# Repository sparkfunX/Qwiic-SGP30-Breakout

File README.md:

Qwiic SGP30 Breakout
===========================================================

[*SparkX SGP30 Breakout (Qwiic) (SPX-14813)*](https://www.sparkfun.com/products/14813)

The SGP30 is an indoor air quality sensor equipped with an I<sup>2</sup>C interface. It outputs equivalent CO<sub>2</sub> in ppm and Total Volatile Organic Compounds (TVOC) in ppb. The sensor also gives access to its raw measurement values of Ethanol and H<sub>2</sub>. 

The SGP30 boasts high stability with low long term drift. With its continuous baseline compensation algorithm, readings stay accurate over time. You can even fine tune your readings by interfacing with an external humidity sensor to add humidity compensation.
While the CCS811 requires a burn-in of 48 hours and a run-in of 20 minutes the SGP30 is ready to go after just 15 seconds.

This board is one of our many [Qwiic](https://www.sparkfun.com/qwiic) compatible boards! Simply plug and go. No soldering, no figuring out which is SDA or SCL, and no voltage regulation or translation required!

SparkFun labored with love to create this. Feel like supporting open source hardware? 
Buy a [board](https://www.sparkfun.com/products/14813) from SparkFun!

Repository Contents
-------------------

* **/Hardware** - Eagle design files (.brd, .sch)

Library
--------------
* **[Arduino Library](https://github.com/sparkfun/SparkFun_SGP30_Library)** - Library for SGP30

License Information
-------------------

This product is _**open source**_! 

If you have any questions or concerns on licensing, please contact techsupport@sparkfun.com.

Please use, reuse, and modify these files as you see fit. Please maintain attribution to SparkFun Electronics and release any derivative under the same license.

Distributed as-is; no warranty is given.

- Your friends at SparkFun.

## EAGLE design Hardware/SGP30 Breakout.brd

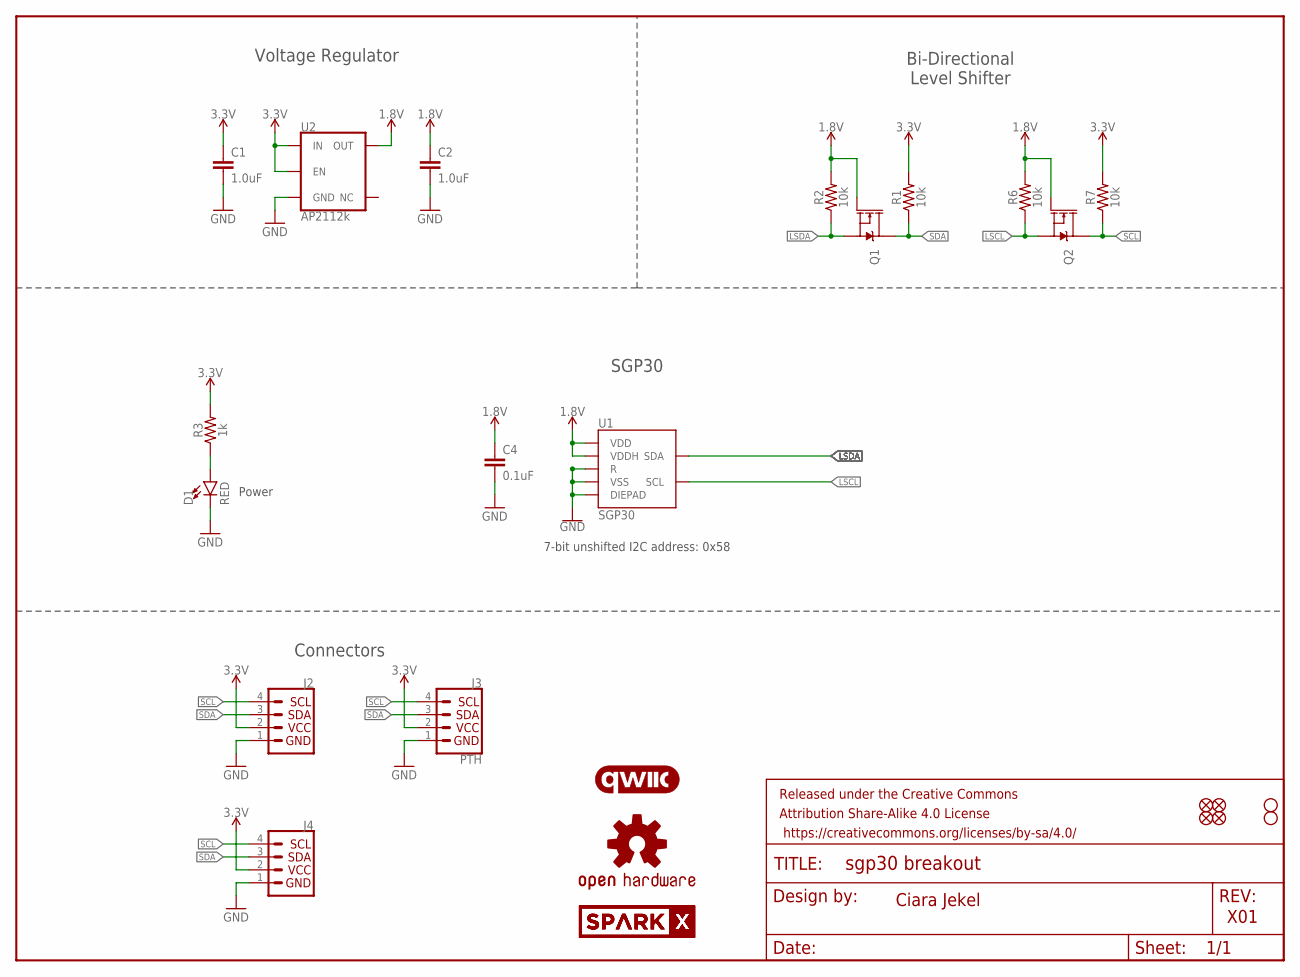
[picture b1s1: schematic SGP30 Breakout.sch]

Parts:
C1, C2: 1.0uF; 0603
C4: 0.1uF; 0603
D1: RED; LED-0603
FRAME1: FRAME-LETTER; CREATIVE_COMMONS
J2, J4: QWIIC_CONNECTORJS-1MM; 1X04_1MM_RA
J3: PTH; 1X04_NO_SILK
JP1, JP2, JP5, JP6: FIDUCIALUFIDUCIAL; MICRO-FIDUCIAL
JP3, JP4: STAND-OFF
LOGO1: OSHW-LOGOMINI; OSHW-LOGO-MINI
Q1, Q2: MOSFET-NCH-BSS138; SOT23-3
R1, R2, R6, R7: 10k; 0603
R3: 1k; 0603
U1: SGP30
U2: AP2112k; SOT23-5
U$1, U$2: SPARKX-LOGO4; SPARKX-MEDIUM
U$9: QWIIC_LOGO_7MM; QWIIC_7MM

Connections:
1.8V: C2.1, C4.1, Q1.1 (G), Q2.1 (G), R2.2, R6.2, U1.1 (VDD), U1.5 (VDDH), U2.5 (OUT)
3.3V: C1.1, J2.2, J3.2 (VCC), J4.2, R1.2, R3.2, R7.2, U2.1 (IN), U2.3 (EN)
GND: C1.2, C2.2, C4.2, D1.C, J2.1, J3.1 (GND), J4.1, U1.2 (VSS), U1.4 (R), U1.DIEPAD, U2.2 (GND)
LSCL: Q2.2 (S), R6.1, U1.6 (SCL)
LSDA: Q1.2 (S), R2.1, U1.3 (SDA)
unnamed: D1.A, R3.1
SCL: J2.4, J3.4 (SCL), J4.4, Q2.3 (D), R7.1
SDA: J2.3, J3.3 (SDA), J4.3, Q1.3 (D), R1.1

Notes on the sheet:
Ciara Jekel
X01
7-bit unshifted I2C address: 0x58
Power
Bi-Directional Level Shifter
Voltage Regulator
SGP30
Connectors

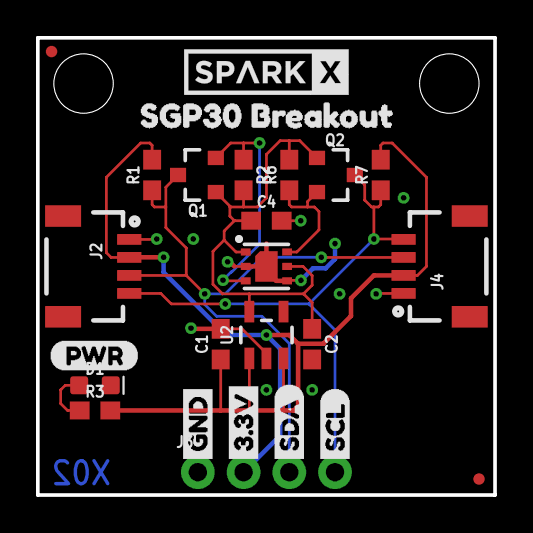
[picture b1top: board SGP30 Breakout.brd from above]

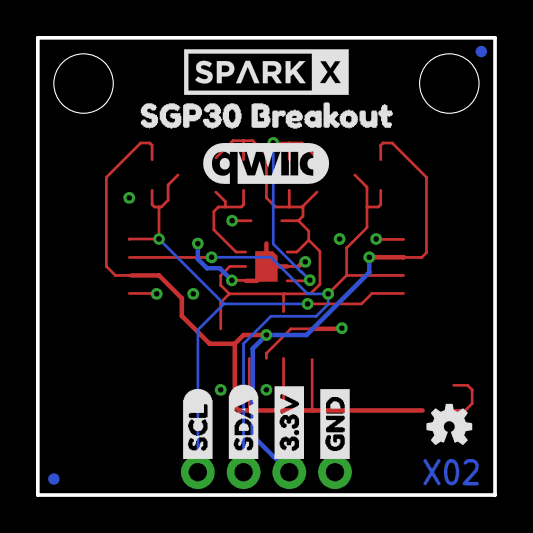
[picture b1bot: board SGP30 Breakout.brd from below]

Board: 2 copper layers, 25.4 x 25.4 mm, 38 parts (10 on the bottom side), 8 nets.

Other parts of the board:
U$3, U$22: GND1
U$4, U$21: 3#3V2
U$5, U$27: SDA8
U$6, U$26: SCL9
U$7, U$8: SGP30_BREAKOUT1
U$10: (PWR)

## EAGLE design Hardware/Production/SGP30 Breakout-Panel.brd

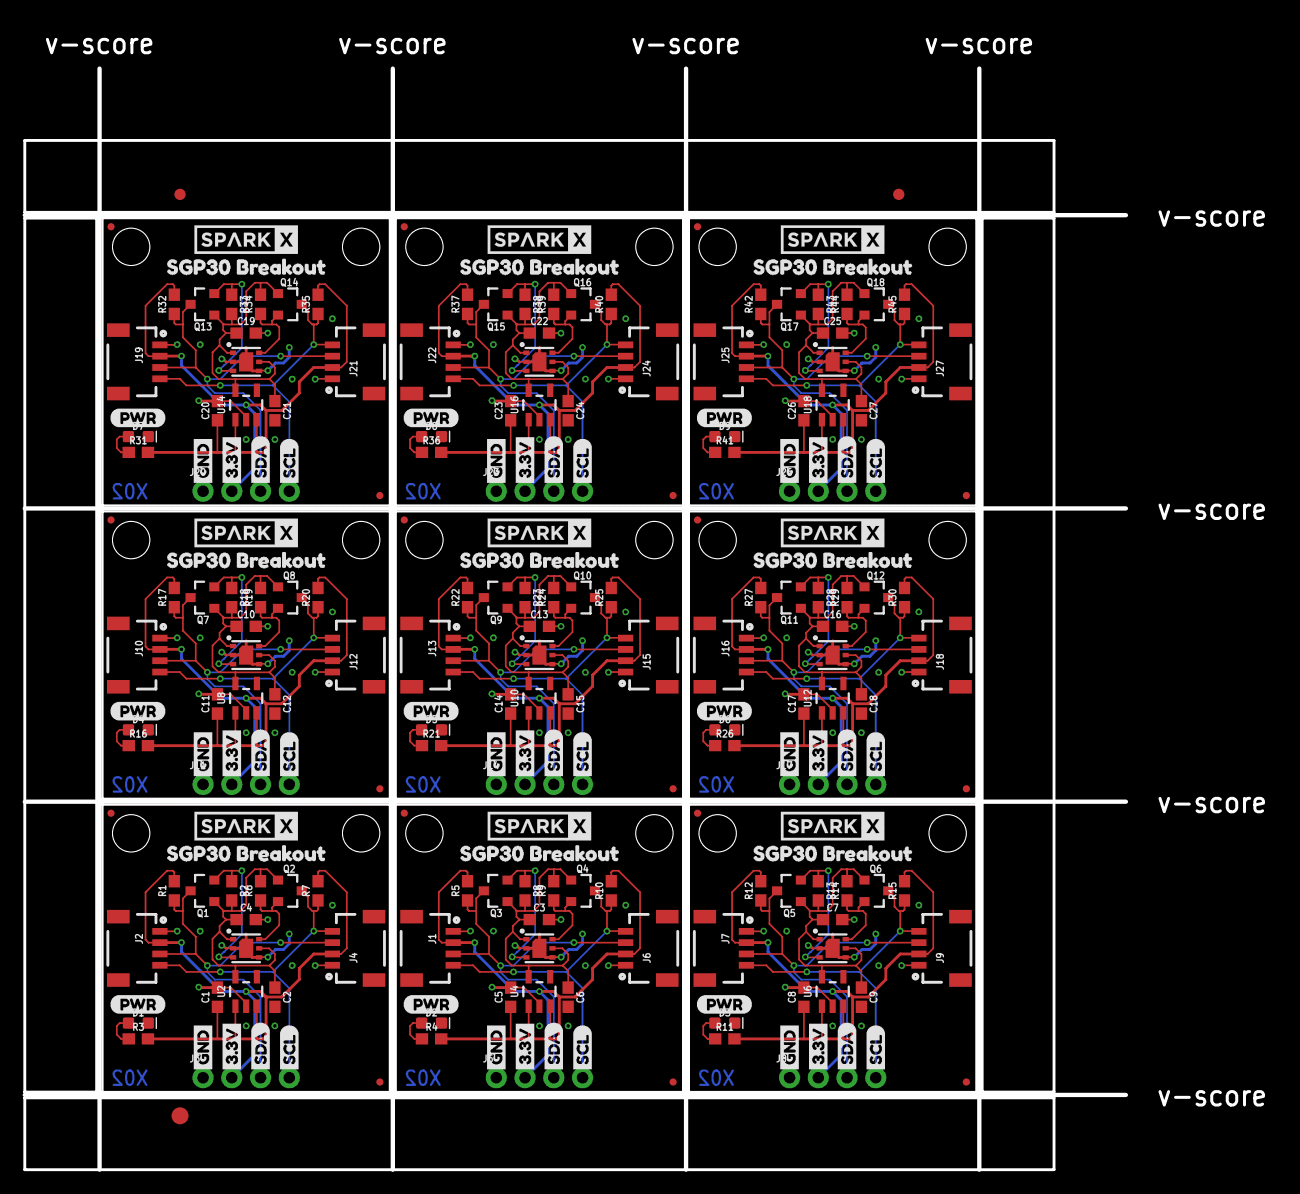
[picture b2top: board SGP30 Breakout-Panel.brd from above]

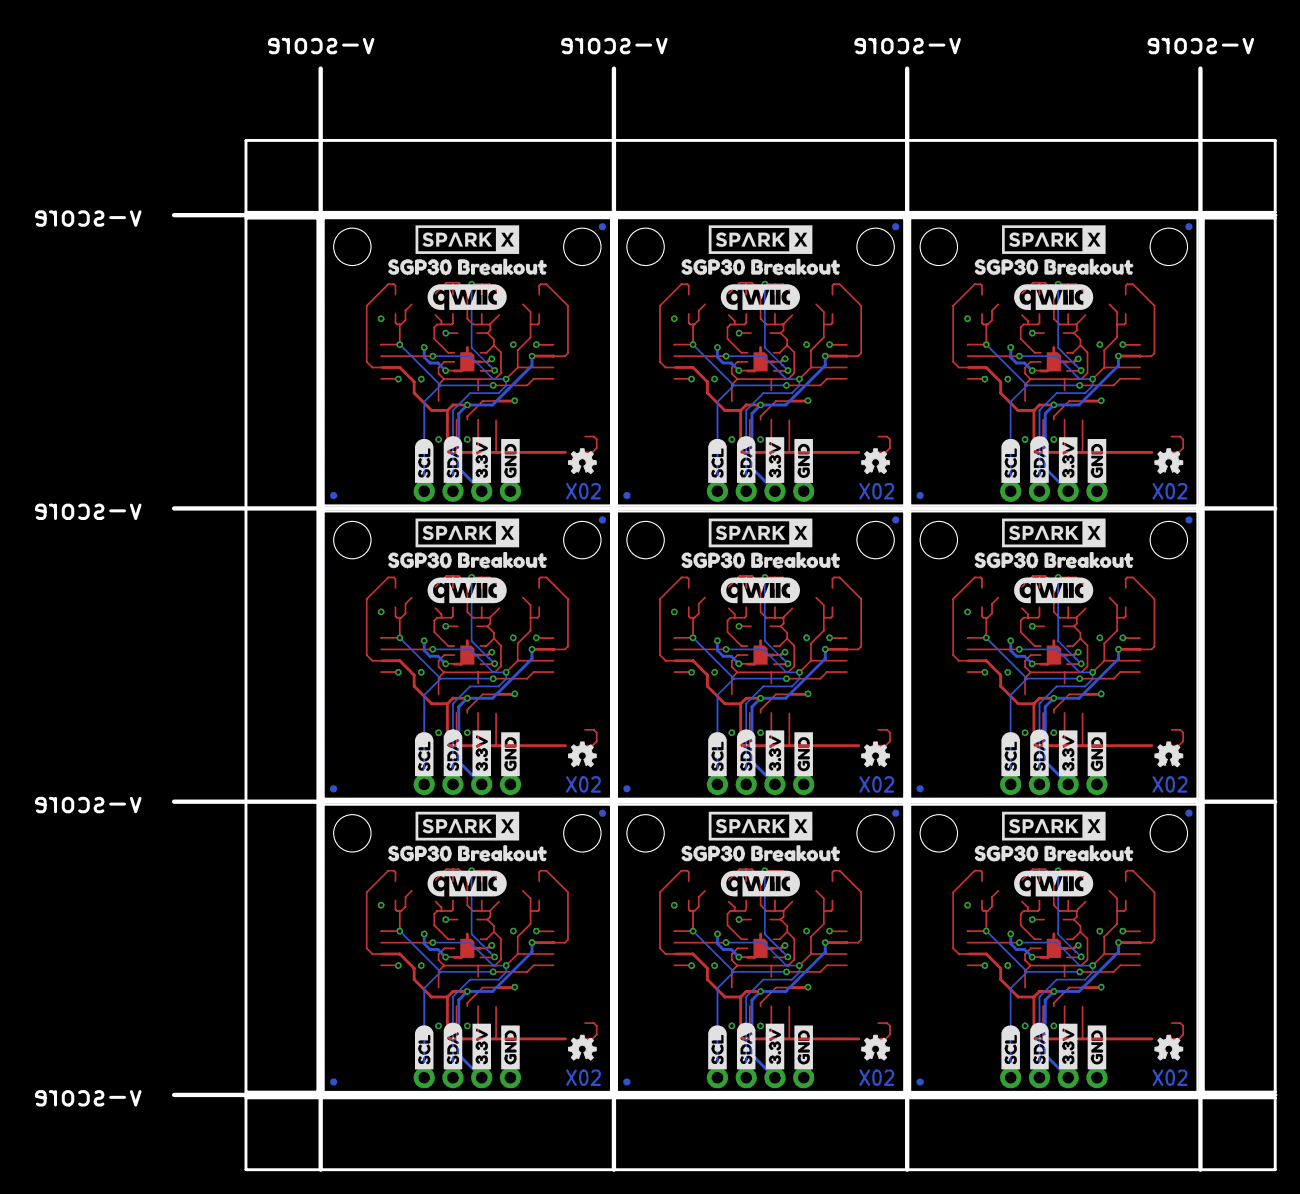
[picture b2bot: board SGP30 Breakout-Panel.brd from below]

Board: 2 copper layers, 110.5 x 101.2 mm, 336 parts (90 on the bottom side), 72 nets.

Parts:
C1, C2, C5, C6, C8, C9, C11, C12, C14, C15, C17, C18, C20, C21, C23, C24, C26, C27: 1.0uF; 0603
C3, C4, C7, C10, C13, C16, C19, C22, C25: 0.1uF; 0603
D1, D2, D3, D4, D5, D6, D7, D8, D9: RED; LED-0603
E$1, E$2: FIDUCIAL-1X2
E$3: FIDUCIAL-1.5X3
J1, J2, J4, J6, J7, J9, J10, J12, J13, J15, J16, J18, J19, J21, J22, J24, J25, J27: 1X04_1MM_RA
J3, J5, J8, J11, J14, J17, J20, J23, J26: PTH; 1X04_NO_SILK
JP1, JP2, JP5, JP6, JP9, JP10, JP11, JP12, JP15, JP16, JP17, JP18, JP21, JP22, JP23, JP24, JP27, JP28, JP29, JP30, JP33, JP34, JP35, JP36, JP39, JP40, JP41, JP42, JP45, JP46, JP47, JP48, JP51, JP52, JP53, JP54: FIDUCIALUFIDUCIAL; MICRO-FIDUCIAL
JP3, JP4, JP7, JP8, JP13, JP14, JP19, JP20, JP25, JP26, JP31, JP32, JP37, JP38, JP43, JP44, JP49, JP50: STAND-OFF
LOGO1, LOGO2, LOGO3, LOGO4, LOGO5, LOGO6, LOGO7, LOGO8, LOGO9: OSHW-LOGOMINI; OSHW-LOGO-MINI
Q1, Q2, Q3, Q4, Q5, Q6, Q7, Q8, Q9, Q10, Q11, Q12, Q13, Q14, Q15, Q16, Q17, Q18: SOT23-3
R1, R2, R5, R6, R7, R8, R9, R10, R12, R13, R14, R15, R17, R18, R19, R20, R22, R23, R24, R25, R27, R28, R29, R30, R32, R33, R34, R35, R37, R38, R39, R40, R42, R43, R44, R45: 10k; 0603
R3, R4, R11, R16, R21, R26, R31, R36, R41: 1k; 0603
U1, U3, U5, U7, U9, U11, U13, U15, U17: SGP30
U2, U4, U6, U8, U10, U12, U14, U16, U18: AP2112k; SOT23-5
U$1, U$2, U$11, U$12, U$29, U$30, U$43, U$44, U$57, U$58, U$71, U$72, U$85, U$86, U$99, U$100, U$113, U$114: SPARKX-LOGO4; SPARKX-MEDIUM
U$3, U$14, U$17, U$22, U$32, U$35, U$46, U$49, U$60, U$63, U$74, U$77, U$88, U$91, U$102, U$105, U$116, U$119: GND1
U$4, U$13, U$18, U$21, U$31, U$36, U$45, U$50, U$59, U$64, U$73, U$78, U$87, U$92, U$101, U$106, U$115, U$120: 3#3V2
U$5, U$16, U$19, U$27, U$34, U$37, U$48, U$51, U$62, U$65, U$76, U$79, U$90, U$93, U$104, U$107, U$118, U$121: SDA8
U$6, U$15, U$20, U$26, U$33, U$38, U$47, U$52, U$61, U$66, U$75, U$80, U$89, U$94, U$103, U$108, U$117, U$122: SCL9
U$7, U$8, U$24, U$25, U$40, U$41, U$54, U$55, U$68, U$69, U$82, U$83, U$96, U$97, U$110, U$111, U$124, U$125: SGP30_BREAKOUT1
U$9, U$28, U$42, U$56, U$70, U$84, U$98, U$112, U$126: QWIIC_LOGO_7MM; QWIIC_7MM
U$10, U$23, U$39, U$53, U$67, U$81, U$95, U$109, U$123: (PWR)

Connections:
1.8V: C2.1, C4.1, Q1.1, Q2.1, R2.2, R6.2, U1.1, U1.5, U2.5
1.8V1: C3.1, C6.1, Q3.1, Q4.1, R8.2, R9.2, U3.1, U3.5, U4.5
1.8V2: C7.1, C9.1, Q5.1, Q6.1, R13.2, R14.2, U5.1, U5.5, U6.5
1.8V3: C10.1, C12.1, Q7.1, Q8.1, R18.2, R19.2, U7.1, U7.5, U8.5
1.8V4: C13.1, C15.1, Q9.1, Q10.1, R23.2, R24.2, U9.1, U9.5, U10.5
1.8V5: C16.1, C18.1, Q11.1, Q12.1, R28.2, R29.2, U11.1, U11.5, U12.5
1.8V6: C19.1, C21.1, Q13.1, Q14.1, R33.2, R34.2, U13.1, U13.5, U14.5
1.8V7: C22.1, C24.1, Q15.1, Q16.1, R38.2, R39.2, U15.1, U15.5, U16.5
1.8V8: C25.1, C27.1, Q17.1, Q18.1, R43.2, R44.2, U17.1, U17.5, U18.5
3.3V: C1.1, J2.2, J3.2, J4.2, R1.2, R3.2, R7.2, U2.1, U2.3
3.3V1: C5.1, J1.2, J5.2, J6.2, R4.2, R5.2, R10.2, U4.1, U4.3
3.3V2: C8.1, J7.2, J8.2, J9.2, R11.2, R12.2, R15.2, U6.1, U6.3
3.3V3: C11.1, J10.2, J11.2, J12.2, R16.2, R17.2, R20.2, U8.1, U8.3
3.3V4: C14.1, J13.2, J14.2, J15.2, R21.2, R22.2, R25.2, U10.1, U10.3
3.3V5: C17.1, J16.2, J17.2, J18.2, R26.2, R27.2, R30.2, U12.1, U12.3
3.3V6: C20.1, J19.2, J20.2, J21.2, R31.2, R32.2, R35.2, U14.1, U14.3
3.3V7: C23.1, J22.2, J23.2, J24.2, R36.2, R37.2, R40.2, U16.1, U16.3
3.3V8: C26.1, J25.2, J26.2, J27.2, R41.2, R42.2, R45.2, U18.1, U18.3
GND: C1.2, C2.2, C4.2, D1.C, J2.1, J3.1, J4.1, U1.2, U1.4, U1.DIEPAD, U2.2
GND1: C3.2, C5.2, C6.2, D2.C, J1.1, J5.1, J6.1, U3.2, U3.4, U3.DIEPAD, U4.2
GND2: C7.2, C8.2, C9.2, D3.C, J7.1, J8.1, J9.1, U5.2, U5.4, U5.DIEPAD, U6.2
GND3: C10.2, C11.2, C12.2, D4.C, J10.1, J11.1, J12.1, U7.2, U7.4, U7.DIEPAD, U8.2
GND4: C13.2, C14.2, C15.2, D5.C, J13.1, J14.1, J15.1, U9.2, U9.4, U9.DIEPAD, U10.2
GND5: C16.2, C17.2, C18.2, D6.C, J16.1, J17.1, J18.1, U11.2, U11.4, U11.DIEPAD, U12.2
GND6: C19.2, C20.2, C21.2, D7.C, J19.1, J20.1, J21.1, U13.2, U13.4, U13.DIEPAD, U14.2
GND7: C22.2, C23.2, C24.2, D8.C, J22.1, J23.1, J24.1, U15.2, U15.4, U15.DIEPAD, U16.2
GND8: C25.2, C26.2, C27.2, D9.C, J25.1, J26.1, J27.1, U17.2, U17.4, U17.DIEPAD, U18.2
LSCL: Q2.2, R6.1, U1.6
LSCL1: Q4.2, R9.1, U3.6
LSCL2: Q6.2, R14.1, U5.6
LSCL3: Q8.2, R19.1, U7.6
LSCL4: Q10.2, R24.1, U9.6
LSCL5: Q12.2, R29.1, U11.6
LSCL6: Q14.2, R34.1, U13.6
LSCL7: Q16.2, R39.1, U15.6
LSCL8: Q18.2, R44.1, U17.6
LSDA: Q1.2, R2.1, U1.3
LSDA1: Q3.2, R8.1, U3.3
LSDA2: Q5.2, R13.1, U5.3
LSDA3: Q7.2, R18.1, U7.3
LSDA4: Q9.2, R23.1, U9.3
LSDA5: Q11.2, R28.1, U11.3
LSDA6: Q13.2, R33.1, U13.3
LSDA7: Q15.2, R38.1, U15.3
LSDA8: Q17.2, R43.1, U17.3
unnamed: D2.A, R4.1
unnamed: D3.A, R11.1
unnamed: D1.A, R3.1
unnamed: D4.A, R16.1
unnamed: D5.A, R21.1
unnamed: D6.A, R26.1
unnamed: D7.A, R31.1
unnamed: D8.A, R36.1
unnamed: D9.A, R41.1
SCL: J2.4, J3.4, J4.4, Q2.3, R7.1
SCL1: J1.4, J5.4, J6.4, Q4.3, R10.1
SCL2: J7.4, J8.4, J9.4, Q6.3, R15.1
SCL3: J10.4, J11.4, J12.4, Q8.3, R20.1
SCL4: J13.4, J14.4, J15.4, Q10.3, R25.1
SCL5: J16.4, J17.4, J18.4, Q12.3, R30.1
SCL6: J19.4, J20.4, J21.4, Q14.3, R35.1
SCL7: J22.4, J23.4, J24.4, Q16.3, R40.1
SCL8: J25.4, J26.4, J27.4, Q18.3, R45.1
SDA: J2.3, J3.3, J4.3, Q1.3, R1.1
SDA1: J1.3, J5.3, J6.3, Q3.3, R5.1
SDA2: J7.3, J8.3, J9.3, Q5.3, R12.1
SDA3: J10.3, J11.3, J12.3, Q7.3, R17.1
SDA4: J13.3, J14.3, J15.3, Q9.3, R22.1
SDA5: J16.3, J17.3, J18.3, Q11.3, R27.1
SDA6: J19.3, J20.3, J21.3, Q13.3, R32.1
SDA7: J22.3, J23.3, J24.3, Q15.3, R37.1
SDA8: J25.3, J26.3, J27.3, Q17.3, R42.1

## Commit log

2018-06-22 added section labels
2018-06-28 fixed missing ground connection
2018-10-02 add issue template
2019-03-14 Fixed ground connections
    * Pad not grounded
    * Connected pad to solde mask
2020-02-07 Added plug-and-play test script

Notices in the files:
parts and their libraries:
SparkFun-Resistors: Licensing: Creative Commons ShareAlike 4.0 International - https://creativecommons.org/licenses/by-sa/4.0
SparkFun-Aesthetics: Released under the Creative Commons Attribution Share-Alike 4.0 License
SparkFun-Aesthetics: https://creativecommons.org/licenses/by-sa/4.0
